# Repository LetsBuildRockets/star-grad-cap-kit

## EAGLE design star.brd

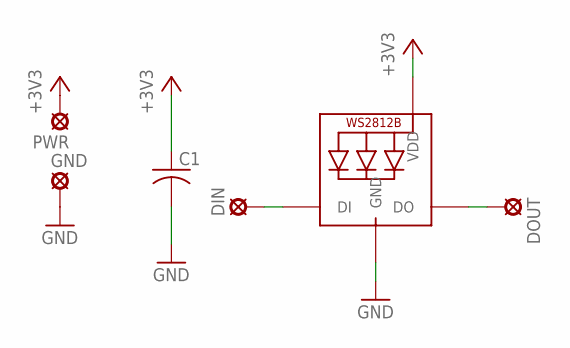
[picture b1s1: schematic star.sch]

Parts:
C1: C-USC0402K; C0402K
DIN: 50THOU
DOUT: 50THOU
GND: 50THOU
LED1: WS2812B5050; WS2812B
PWR: 50THOU

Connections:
+3V3: C1.1, LED1.1-VDD (VDD), PWR.P$1
GND: C1.2, GND.P$1, LED1.3-GND (GND)
unnamed: DIN.P$1, LED1.4-DIN (DI)
unnamed: DOUT.P$1, LED1.2-DOUT (DO)

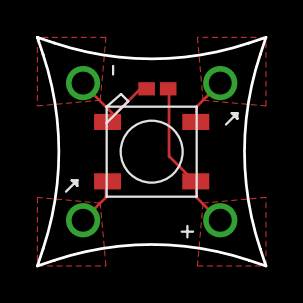
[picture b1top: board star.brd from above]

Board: 2 copper layers, 12.7 x 12.7 mm, 7 parts (1 on the bottom side), 4 nets.

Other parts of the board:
U$1: LOGO-0.30"

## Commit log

2017-06-19 add star board files
